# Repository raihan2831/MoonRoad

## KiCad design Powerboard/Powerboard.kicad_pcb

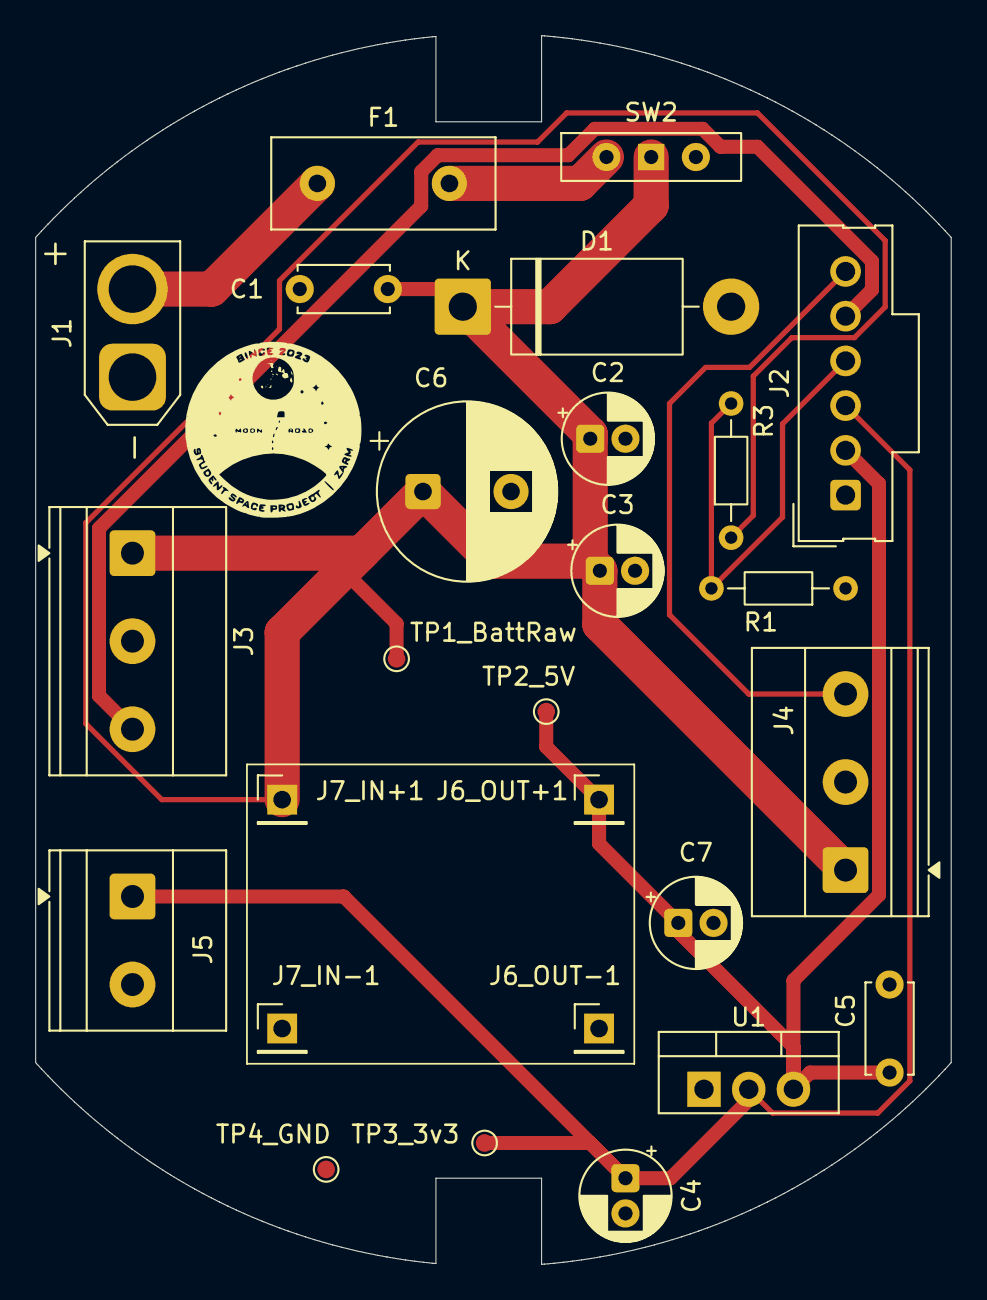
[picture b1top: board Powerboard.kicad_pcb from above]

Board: 2 copper layers, 52.0 x 69.8 mm, 26 parts (0 on the bottom side), 9 nets.

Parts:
C1, C5: 100 nF; C_Disc_D5.0mm_W2.5mm_P5.00mm
C2: 470 uF; CP_Radial_D5.0mm_P2.00mm
C3, C7: 100 uF; CP_Radial_D5.0mm_P2.00mm
C4: 10 uF; CP_Radial_D5.0mm_P2.00mm
C6: 1000 uF; CP_Radial_D10.0mm_P5.00mm
D1: 1N5822; D_DO-201AD_P15.24mm_Horizontal
F1: Polyfuse; C_Disc_D12.5mm_W5.0mm_P7.50mm
J1: XT60 Batt connector; AMASS_XT30U-F_1x02_P5.0mm_Vertical
J2: Molex 70543-0005_FlightComp; Molex_SL_171971-0006_1x06_P2.54mm_Vertical
J3: Screw_Terminal_01x03_Servo1; TerminalBlock_Phoenix_MKDS-1,5-3_1x03_P5.00mm_Horizontal
J4: Screw_Terminal_01x03_Servo2; TerminalBlock_Phoenix_MKDS-1,5-3_1x03_P5.00mm_Horizontal
J5: Screw_Terminal_01x02_IMU; TerminalBlock_Phoenix_MKDS-1,5-2_1x02_P5.00mm_Horizontal
J6_OUT+1, J6_OUT-1, J7_IN+1, J7_IN-1: Conn_01x01_Pin; PinHeader_1x01_P2.54mm_Vertical
R1: 3.3 k; R_Axial_DIN0204_L3.6mm_D1.6mm_P7.62mm_Horizontal
R3: 10 k; R_Axial_DIN0204_L3.6mm_D1.6mm_P7.62mm_Horizontal
SW2: SW_SPDT; SW_Slide-03_Wuerth-WS-SLTV_10x2.5x6.4_P2.54mm
TP1_BattRaw: TestPoint_BattRaw; TestPoint_Pad_D1.0mm
TP2_5V: TestPoint_5V; TestPoint_Pad_D1.0mm
TP3_3v3: TestPoint_3v3; TestPoint_Pad_D1.0mm
TP4_GND: TestPoint_GND; TestPoint_Pad_D1.0mm
U1: LD1117V33; TO-220-3_Vertical

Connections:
/3.3V_OUT: C4.1, J2.3, J5.1, TP3_3v3.1, U1.2 (VO)
/5V_OUT: C5.1, C7.1, J2.2, J6_OUT+1.1, TP2_5V.1, U1.3 (VI)
/+Batt_Fused: F1.2, SW2.2 (B)
/+Batt_In: F1.1, J1.2
/+Batt_Raw: C1.2, C2.1, C3.1, C6.1, D1.1 (K), J3.1, J4.1, J7_IN+1.1, R3.1, SW2.1 (A), TP1_BattRaw.1
/BATT_MONITOR: J2.4, R1.2, R3.2
/PWM_Pitch: J2.5, J3.3
/PWM_Yaw: J2.6, J4.3
GND: C1.1, C2.2, C3.2, C4.2, C5.2, C6.2, C7.2, D1.2 (A), J1.1, J2.1, J3.2, J4.2, J5.2, J6_OUT-1.1, J7_IN-1.1, R1.1, TP4_GND.1, U1.1 (GND)
